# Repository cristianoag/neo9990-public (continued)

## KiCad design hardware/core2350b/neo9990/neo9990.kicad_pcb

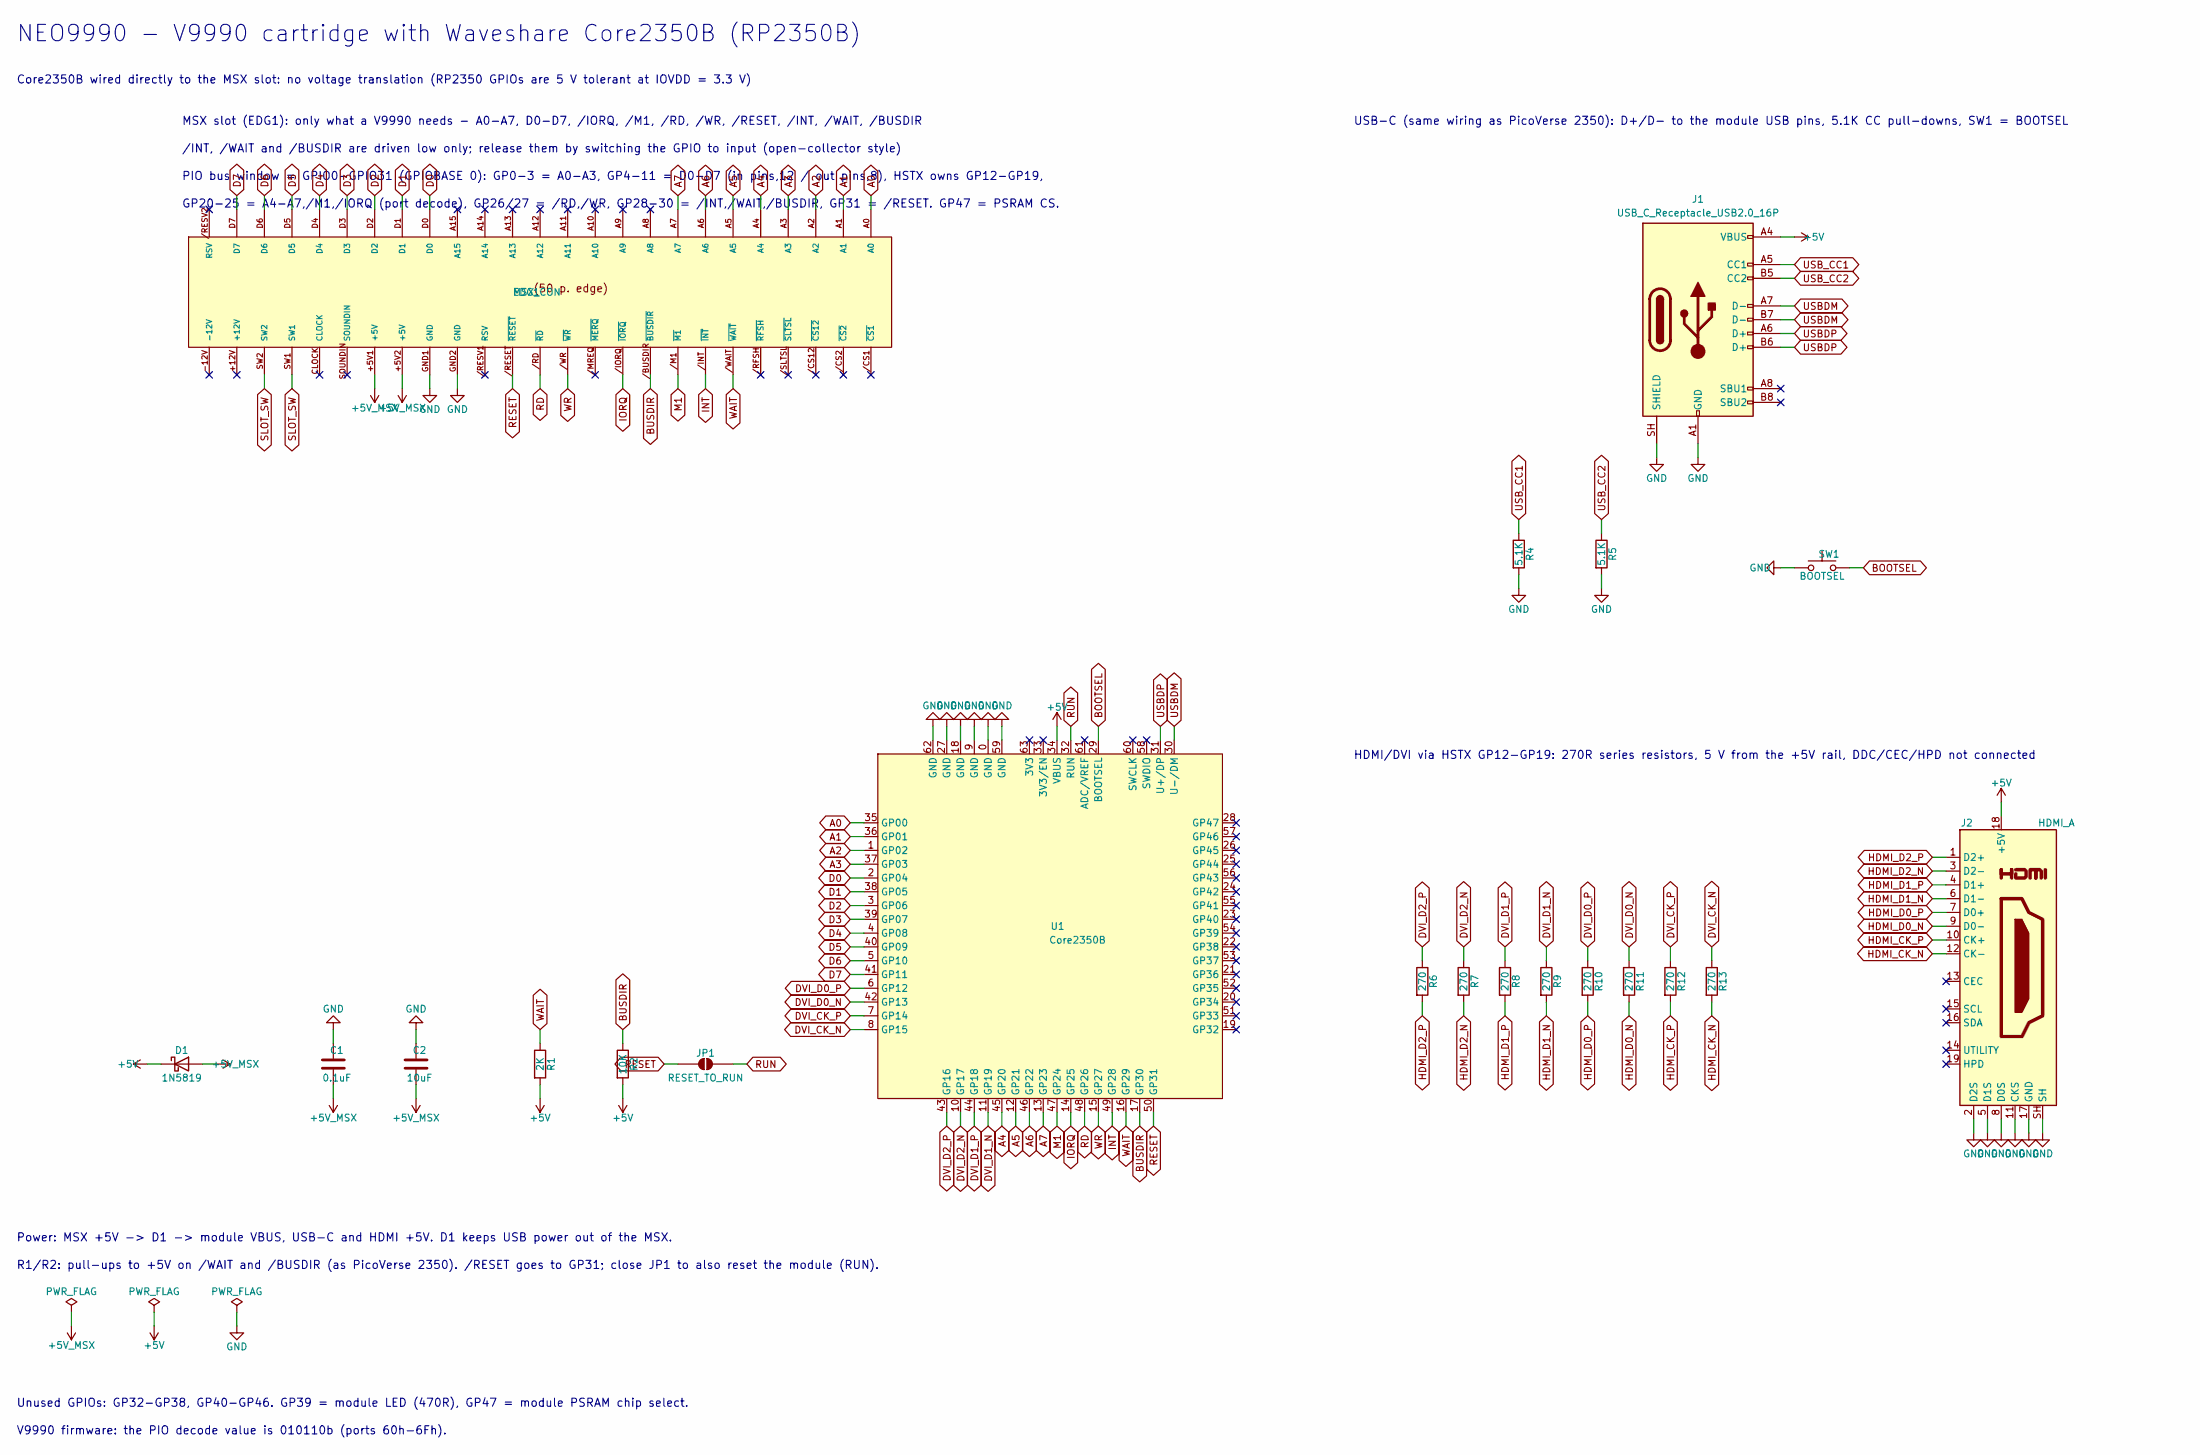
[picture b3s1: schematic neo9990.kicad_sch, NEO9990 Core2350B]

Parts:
C1: 0.1uF; C_0603_1608Metric_Pad1.08x0.95mm_HandSolder
C2: 10uF; C_0603_1608Metric_Pad1.08x0.95mm_HandSolder
D1: 1N5819; D_SOD-123
EDG1: MSX_CON; msx-con-MSXCART
J1: USB_C_Receptacle_USB2.0_16P; USB_C_Receptacle_HRO_TYPE-C-31-M-12
J2: HDMI_A; TE_1747981-2
JP1: RESET_TO_RUN; SolderJumper-2_P1.3mm_Open_RoundedPad1.0x1.5mm
R1: 2K; R_0603_1608Metric_Pad0.98x0.95mm_HandSolder
R2: 10K; R_0603_1608Metric_Pad0.98x0.95mm_HandSolder
R4, R5: 5.1K; R_0603_1608Metric_Pad0.98x0.95mm_HandSolder
R6, R7, R8, R9, R10, R11, R12, R13: 270; R_0603_1608Metric_Pad0.98x0.95mm_HandSolder
SW1: BOOTSEL; SW_Push_1P1T_NO_E-Switch_TL3301NxxxxxG
U1: Core2350B; Core2350

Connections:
+5V: D1.1 (K), J1.A4 (VBUS), J1.A9 (VBUS), J1.B4 (VBUS), J1.B9 (VBUS), J2.18 (+5V), R1.2, R2.2, U1.34 (VBUS)
+5V_MSX: C1.2, C2.2, D1.2 (A), EDG1.+5V1 (+5V), EDG1.+5V2 (+5V)
A0: EDG1.A0, U1.35 (GP00)
A1: EDG1.A1, U1.36 (GP01)
A2: EDG1.A2, U1.1 (GP02)
A3: EDG1.A3, U1.37 (GP03)
A4: EDG1.A4, U1.45 (GP20)
A5: EDG1.A5, U1.12 (GP21)
A6: EDG1.A6, U1.46 (GP22)
A7: EDG1.A7, U1.13 (GP23)
BOOTSEL: SW1.2, U1.29 (BOOTSEL)
BUSDIR: EDG1./BUSDIR (~BUSDIR), R2.1, U1.17 (GP30)
D0: EDG1.D0, U1.2 (GP04)
D1: EDG1.D1, U1.38 (GP05)
D2: EDG1.D2, U1.3 (GP06)
D3: EDG1.D3, U1.39 (GP07)
D4: EDG1.D4, U1.4 (GP08)
D5: EDG1.D5, U1.40 (GP09)
D6: EDG1.D6, U1.5 (GP10)
D7: EDG1.D7, U1.41 (GP11)
DVI_CK_N: R13.1, U1.8 (GP15)
DVI_CK_P: R12.1, U1.7 (GP14)
DVI_D0_N: R11.1, U1.42 (GP13)
DVI_D0_P: R10.1, U1.6 (GP12)
DVI_D1_N: R9.1, U1.11 (GP19)
DVI_D1_P: R8.1, U1.44 (GP18)
DVI_D2_N: R7.1, U1.10 (GP17)
DVI_D2_P: R6.1, U1.43 (GP16)
GND: C1.1, C2.1, EDG1.GND1 (GND), EDG1.GND2 (GND), J1.A1 (GND), J1.A12 (GND), J1.B1 (GND), J1.B12 (GND), J1.SH (SHIELD), J2.2 (D2S), J2.5 (D1S), J2.8 (D0S), J2.11 (CKS), J2.17 (GND), J2.SH, R4.2, R5.2, SW1.1, U1.0 (GND), U1.9 (GND), U1.18 (GND), U1.27 (GND), U1.59 (GND), U1.62 (GND)
HDMI_CK_N: J2.12 (CK-), R13.2
HDMI_CK_P: J2.10 (CK+), R12.2
HDMI_D0_N: J2.9 (D0-), R11.2
HDMI_D0_P: J2.7 (D0+), R10.2
HDMI_D1_N: J2.6 (D1-), R9.2
HDMI_D1_P: J2.4 (D1+), R8.2
HDMI_D2_N: J2.3 (D2-), R7.2
HDMI_D2_P: J2.1 (D2+), R6.2
INT: EDG1./INT (~INT), U1.49 (GP28)
IORQ: EDG1./IORQ (~IORQ), U1.14 (GP25)
M1: EDG1./M1 (~M1), U1.47 (GP24)
RD: EDG1./RD (~RD), U1.48 (GP26)
RESET: EDG1./RESET (~RESET), JP1.1 (A), U1.50 (GP31)
RUN: JP1.2 (B), U1.32 (RUN)
SLOT_SW: EDG1.SW1, EDG1.SW2
USBDM: J1.A7 (D-), J1.B7 (D-), U1.30 (U-/DM)
USBDP: J1.A6 (D+), J1.B6 (D+), U1.31 (U+/DP)
USB_CC1: J1.A5 (CC1), R4.1
USB_CC2: J1.B5 (CC2), R5.1
WAIT: EDG1./WAIT (~WAIT), R1.1, U1.16 (GP29)
WR: EDG1./WR (~WR), U1.15 (GP27)

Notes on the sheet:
NEO9990 - V9990 cartridge with Waveshare Core2350B (RP2350B)
Core2350B wired directly to the MSX slot: no voltage translation (RP2350 GPIOs are 5 V tolerant at IOVDD = 3.3 V)
MSX slot (EDG1): only what a V9990 needs - A0-A7, D0-D7, /IORQ, /M1, /RD, /WR, /RESET, /INT, /WAIT, /BUSDIR
/INT, /WAIT and /BUSDIR are driven low only; release them by switching the GPIO to input (open-collector style)
PIO bus window = GPIO0-GPIO31 (GPIOBASE 0): GP0-3 = A0-A3, GP4-11 = D0-D7 (in pins,12 / out pins,8), HSTX owns GP12-GP19,
GP20-25 = A4-A7,/M1,/IORQ (port decode), GP26/27 = /RD,/WR, GP28-30 = /INT,/WAIT,/BUSDIR, GP31 = /RESET. GP47 = PSRAM CS.
Power: MSX +5V -> D1 -> module VBUS, USB-C and HDMI +5V. D1 keeps USB power out of the MSX.
R1/R2: pull-ups to +5V on /WAIT and /BUSDIR (as PicoVerse 2350). /RESET goes to GP31; close JP1 to also reset the module (RUN).
USB-C (same wiring as PicoVerse 2350): D+/D- to the module USB pins, 5.1K CC pull-downs, SW1 = BOOTSEL
HDMI/DVI via HSTX GP12-GP19: 270R series resistors, 5 V from the +5V rail, DDC/CEC/HPD not connected
Unused GPIOs: GP32-GP38, GP40-GP46. GP39 = module LED (470R), GP47 = module PSRAM chip select.
V9990 firmware: the PIO decode value is 010110b (ports 60h-6Fh).

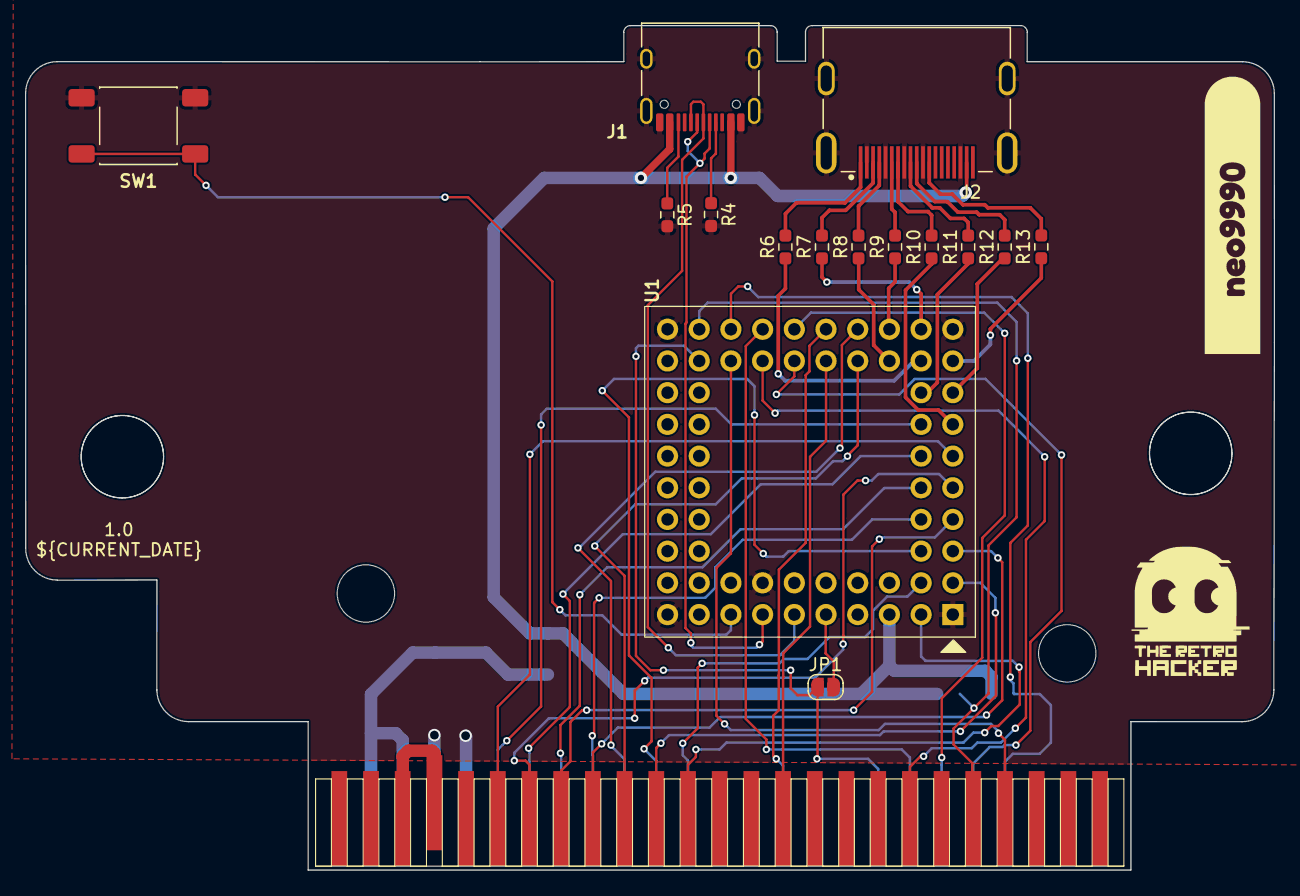
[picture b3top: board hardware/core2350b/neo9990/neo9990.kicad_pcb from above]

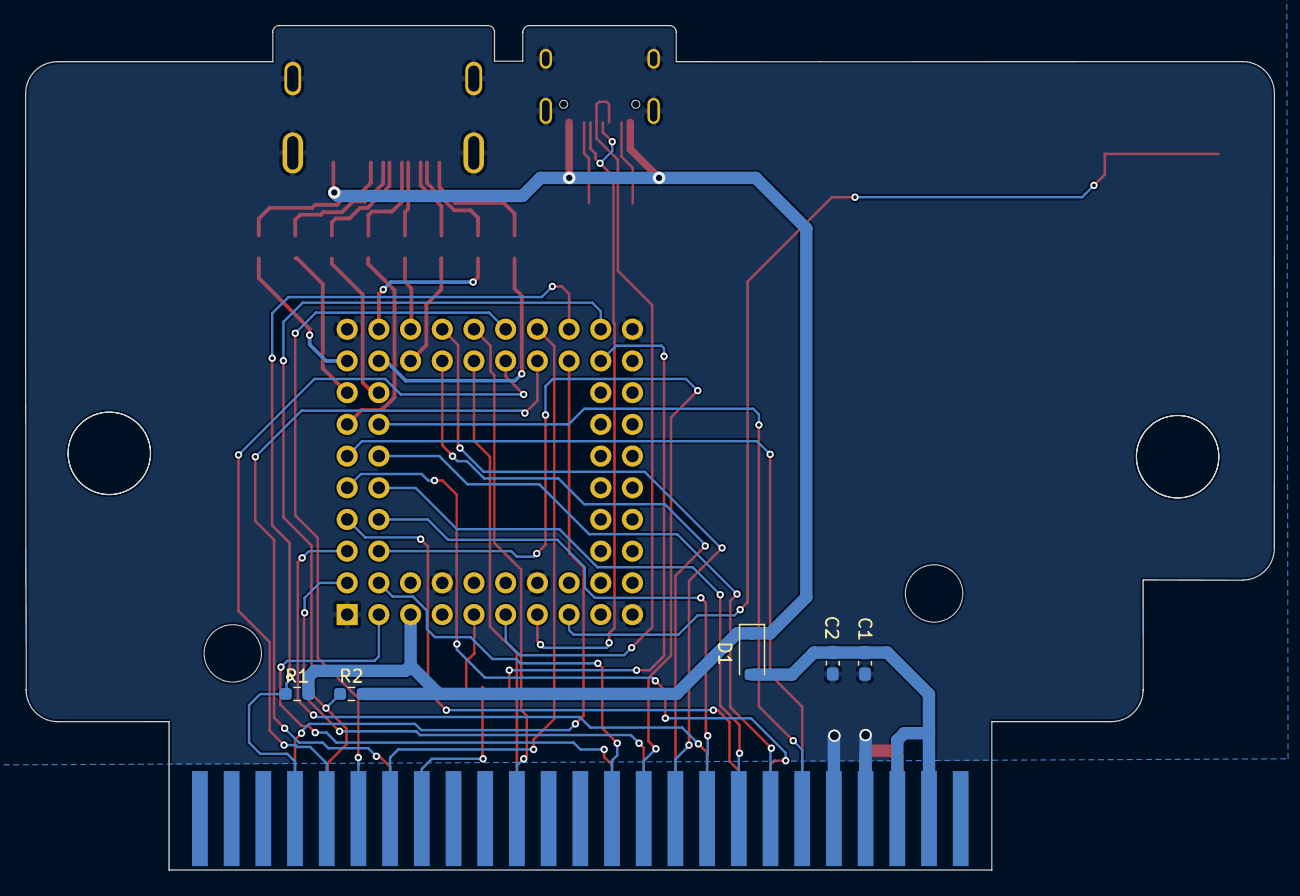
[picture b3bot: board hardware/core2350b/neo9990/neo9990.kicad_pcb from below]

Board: 2 copper layers, 100.1 x 67.7 mm, 22 parts (5 on the bottom side), 50 nets.

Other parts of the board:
kibuzzard-68E299D1: G***; kibuzzard-68E299D1

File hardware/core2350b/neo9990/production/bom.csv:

Designator,Footprint,Quantity,Value,LCSC Part #
C1,0603,1,0.1uF,
C2,0603,1,10uF,
D1,D_SOD-123,1,1N5819,
EDG1,msx-con-MSXCART,1,MSX_CON,
J1,USB_C_Receptacle_HRO_TYPE-C-31-M-12,1,USB_C_Receptacle_USB2.0_16P,
J2,TE_1747981-2,1,HDMI_A,
JP1,SolderJumper-2_P1.3mm_Open_RoundedPad1.0x1.5mm,1,RESET_TO_RUN,
R1,0603,1,2K,
"R10, R11, R12, R13, R6, R7, R8, R9",0603,8,270,
R2,0603,1,10K,
"R4, R5",0603,2,5.1K,
SW1,SW_Push_1P1T_NO_E-Switch_TL3301NxxxxxG,1,BOOTSEL,
U1,Core2350,1,Core2350B,

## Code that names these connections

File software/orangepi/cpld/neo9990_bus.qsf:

set_global_assignment -name FAMILY MAX7000S
set_global_assignment -name DEVICE EPM7160STC100-10
set_global_assignment -name TOP_LEVEL_ENTITY neo9990_bus
set_global_assignment -name ORIGINAL_QUARTUS_VERSION "13.0 SP1"
set_global_assignment -name PROJECT_OUTPUT_DIRECTORY output_files
set_global_assignment -name VERILOG_FILE neo9990_bus.v
set_global_assignment -name VERILOG_INPUT_VERSION VERILOG_2001
set_global_assignment -name MAX7000_DEVICE_IO_STANDARD "3.3-V LVTTL"
set_global_assignment -name ENABLE_JTAG_BST_SUPPORT ON
set_global_assignment -name RESERVE_ALL_UNUSED_PINS_NO_OUTPUT_GND "AS INPUT TRI-STATED"
set_global_assignment -name AUTO_TURBO_BIT ON
set_global_assignment -name SLOW_SLEW_RATE OFF
set_location_assignment PIN_60 -to "msx_a[0]"
set_location_assignment PIN_63 -to "msx_a[1]"
set_location_assignment PIN_67 -to "msx_a[2]"
set_location_assignment PIN_68 -to "msx_a[3]"
set_location_assignment PIN_70 -to "msx_a[4]"
set_location_assignment PIN_72 -to "msx_a[5]"
set_location_assignment PIN_75 -to "msx_a[6]"
set_location_assignment PIN_77 -to "msx_a[7]"
set_location_assignment PIN_79 -to "msx_a[8]"
set_location_assignment PIN_71 -to "msx_a[9]"
set_location_assignment PIN_64 -to "msx_a[10]"
set_location_assignment PIN_69 -to "msx_a[11]"
set_location_assignment PIN_76 -to "msx_a[12]"
set_location_assignment PIN_78 -to "msx_a[13]"
set_location_assignment PIN_96 -to "msx_a[14]"
set_location_assignment PIN_97 -to "msx_a[15]"
set_location_assignment PIN_98 -to "msx_d[0]"
set_location_assignment PIN_50 -to "msx_d[1]"
set_location_assignment PIN_48 -to "msx_d[2]"
set_location_assignment PIN_52 -to "msx_d[3]"
set_location_assignment PIN_53 -to "msx_d[4]"
set_location_assignment PIN_54 -to "msx_d[5]"
set_location_assignment PIN_55 -to "msx_d[6]"
set_location_assignment PIN_57 -to "msx_d[7]"
set_location_assignment PIN_80 -to "msx_iorq_n"
set_location_assignment PIN_65 -to "msx_rd_n"
set_location_assignment PIN_1 -to "msx_wr_n"
set_location_assignment PIN_83 -to "msx_m1_n"
set_location_assignment PIN_85 -to "msx_wait_n"
set_instance_assignment -name AUTO_OPEN_DRAIN ON -to "msx_wait_n"
set_location_assignment PIN_84 -to "msx_int_n"
set_instance_assignment -name AUTO_OPEN_DRAIN ON -to "msx_int_n"
set_location_assignment PIN_81 -to "msx_busdir_n"
set_instance_assignment -name AUTO_OPEN_DRAIN ON -to "msx_busdir_n"
set_location_assignment PIN_92 -to "msx_mreq_n"
set_location_assignment PIN_93 -to "msx_sltsl_n"
set_location_assignment PIN_33 -to "host_d[0]"
set_location_assignment PIN_44 -to "host_d[1]"
set_location_assignment PIN_29 -to "host_d[2]"
set_location_assignment PIN_27 -to "host_d[3]"
set_location_assignment PIN_28 -to "host_d[4]"
set_location_assignment PIN_40 -to "host_d[5]"
set_location_assignment PIN_37 -to "host_d[6]"
set_location_assignment PIN_47 -to "host_d[7]"
set_location_assignment PIN_49 -to "host_d[8]"
set_location_assignment PIN_35 -to "host_d[9]"
set_location_assignment PIN_36 -to "host_d[10]"
set_location_assignment PIN_31 -to "host_d[11]"
set_location_assignment PIN_30 -to "host_d[12]"
set_location_assignment PIN_45 -to "host_d[13]"
set_location_assignment PIN_41 -to "host_d[14]"
set_location_assignment PIN_32 -to "host_d[15]"
set_location_assignment PIN_2 -to "host_sel[0]"
set_location_assignment PIN_5 -to "host_sel[1]"
set_location_assignment PIN_6 -to "host_rd_n"
set_location_assignment PIN_87 -to "host_wr_n"
set_location_assignment PIN_88 -to "host_ready"
set_location_assignment PIN_89 -to "msx_reset_n"
set_location_assignment PIN_90 -to "msx_clk"
set_location_assignment PIN_7 -to "request"
set_location_assignment PIN_8 -to "host_irq_n"
set_location_assignment PIN_9 -to "host_reset_out_n"
set_location_assignment PIN_10 -to "host_msx_clk"
set_location_assignment PIN_94 -to "boot_rom"

set_global_assignment -name LAST_QUARTUS_VERSION "11.0 SP1"

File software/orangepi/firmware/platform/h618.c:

/* SPDX-License-Identifier: GPL-2.0-only */
#include "h618.h"

#define PIO UINT64_C(0x0300b000)
#define PH (PIO + 7u * 0x24u)
#define PI (PIO + 8u * 0x24u)
#define UART UINT64_C(0x05000000)
#define RD (1u << 2)
#define WR (1u << 3)
#define READY (1u << 6)
#define IRQ (1u << 7)

static uint32_t read32(uint64_t address)
{
    uint32_t result = *(volatile uint32_t *)(uintptr_t)address;
    __asm__ volatile("dsb sy" ::: "memory");
    return result;
}

static void write32(uint64_t address, uint32_t value)
{
    __asm__ volatile("dsb sy" ::: "memory");
    *(volatile uint32_t *)(uintptr_t)address = value;
    __asm__ volatile("dsb sy" ::: "memory");
}

static void update(uint64_t address, uint32_t mask, uint32_t value)
{
    write32(address, (read32(address) & ~mask) | (value & mask));
}

uint64_t h618_counter(void)
{
    uint64_t result;
    __asm__ volatile("isb; mrs %0, cntpct_el0" : "=r"(result));
    return result;
}

uint64_t h618_frequency(void)
{
    uint64_t result;
    __asm__ volatile("mrs %0, cntfrq_el0" : "=r"(result));
    return result;
}

void h618_delay_us(unsigned us)
{
    uint64_t start = h618_counter();
    uint64_t duration = (h618_frequency() * us + 999999u) / 1000000u;
    while (h618_counter() - start < duration) __asm__ volatile("yield");
}

static void putc_uart(char c)
{
    for (unsigned tries = 0; tries < 1000000; ++tries) {
        if (read32(UART+0x14) & 0x20) {
            write32(UART, (uint8_t)c);
            return;
        }
    }
    h618_halt();
}

void h618_puts(const char *text)
{
    while (*text) {
        if (*text == '\n') putc_uart('\r');
        putc_uart(*text++);
    }
}

void h618_hex(uint64_t number)
{
    static const char hex[] = "0123456789abcdef";
    h618_puts("0x");
    for (unsigned i = 16; i; --i) putc_uart(hex[(number >> ((i-1)*4)) & 15]);
}

_Noreturn void h618_halt(void)
{
    for (;;) __asm__ volatile("wfe");
}

static void data_direction(bool output)
{
    write32(PI, output ? 0x11111111 : 0);
    write32(PI+4, output ? 0x11111111 : 0);
}

static uint16_t bus_read(void *context, enum neo9990_register reg)
{
    (void)context;
    update(PH+0x10, RD | WR, RD | WR);
    data_direction(false);
    update(PH+0x10, 3u << 4, (unsigned)reg << 4);
    h618_delay_us(1);
    update(PH+0x10, RD, 0);
    h618_delay_us(1);
    uint16_t result = (uint16_t)read32(PI+0x10);
    update(PH+0x10, RD, RD);
    h618_delay_us(1);
    return result;
}

static void bus_write(void *context, enum neo9990_register reg, uint16_t value)
{
    (void)context;
    update(PH+0x10, RD | WR, RD | WR);
    h618_delay_us(1);
    update(PH+0x10, 3u << 4, (unsigned)reg << 4);
    update(PI+0x10, 0xffff, value);
    data_direction(true);
    h618_delay_us(1);
    update(PH+0x10, WR, 0);
    h618_delay_us(1);
    update(PH+0x10, WR, WR);
    h618_delay_us(1);
    data_direction(false);
    h618_delay_us(1);
}

static void bus_ready(void *context, bool high)
{
    (void)context;
    update(PH+0x10, READY, high ? READY : 0);
}

static void bus_irq(void *context, bool asserted)
{
    (void)context;
    update(PH+0x10, IRQ, asserted ? 0 : IRQ);
}

static bool bus_reset(void *context)
{
    (void)context;
    return (read32(PH+0x10) & (1u << 8)) != 0;
}

struct neo_bus h618_bus_init(void)
{
    /* Preload inactive strobes before changing muxes; preserve UART PH0/PH1. */
    update(PH+0x10, 0xfcu, RD | WR | IRQ);
    data_direction(false);
    update(PI+8, 15u, 0); /* PI16 REQUEST input. */
    update(PH, 0xffffff00u, 0x11111100u);
    update(PH+4, 0xffu, 0); /* PH8 RESET and PH9 clock inputs. */
    return (struct neo_bus){.read=bus_read, .write=bus_write, .ready=bus_ready,
                           .irq=bus_irq, .reset_high=bus_reset};
}

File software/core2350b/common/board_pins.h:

/*
 * NEO9990 Core2350B pin assignment. Keep in sync with
 * hardware/core2350b/neo9990/gpio-map.csv and tools/design.py.
 *
 * Everything the PIO reads lives in GPIO0-GPIO31 (PIO GPIOBASE 0):
 *
 *   GP0-GP3     A0-A3          with the data bus: `in pins, 12`
 *   GP4-GP11    D0-D7          `out pins, 8` / `out pindirs, 8`
 *   GP12-GP19   HSTX / DVI     (fixed by the RP2350)
 *   GP20-GP25   A4 A5 A6 A7 /M1 /IORQ   port decode field, bit 0 = GP20
 *   GP26 /RD    GP27 /WR
 *   GP28 /INT   GP29 /WAIT   GP30 /BUSDIR   open collector style: the output
 *                                           latch stays 0, the pin direction
 *                                           asserts (output) or releases (input)
 *   GP31 /RESET
 *   GP39        module red LED (470R): never used for the bus
 *   GP47        module PSRAM chip select
 */
#ifndef BOARD_PINS_H
#define BOARD_PINS_H

/* ---- MSX bus ---- */
#define PIN_A0        0
#define PIN_D0        4
#define PIN_A4        20
#define PIN_M1        24
#define PIN_IORQ      25
#define PIN_RD        26
#define PIN_WR        27
#define PIN_INT       28
#define PIN_WAIT      29
#define PIN_BUSDIR    30
#define PIN_RESET     31

/* Module red LED (470R to GND). Not used: a bus line on this pin would light it
 * and load the MSX data bus. */
#define PIN_LED       39

/* Port decode field: `in pins, 6` from PIN_A4 gives A4 A5 A6 A7 /M1 /IORQ with A4 in
 * bit 0. A cycle is ours when /IORQ = 0, /M1 = 1 (not an interrupt acknowledge) and
 * A7-A4 select the port block. */
#define DECODE_V9990          0x16u   /* A7-A4 = 0110 (ports 60h-6Fh): A5, A6, /M1 high */
#define DECODE_V9968          0x18u   /* A7-A4 = 1000 (ports 80h-8Fh): A7, /M1 high */

/* ---- DVI over HSTX: GPIO 12-19 only ---- */
#define PIN_DVI_D0    12
#define PIN_DVI_CLK   14
#define PIN_DVI_D2    16
#define PIN_DVI_D1    18

/* ---- PSRAM (VRAM) ---- */
#define PIN_PSRAM_CS  47

#endif
